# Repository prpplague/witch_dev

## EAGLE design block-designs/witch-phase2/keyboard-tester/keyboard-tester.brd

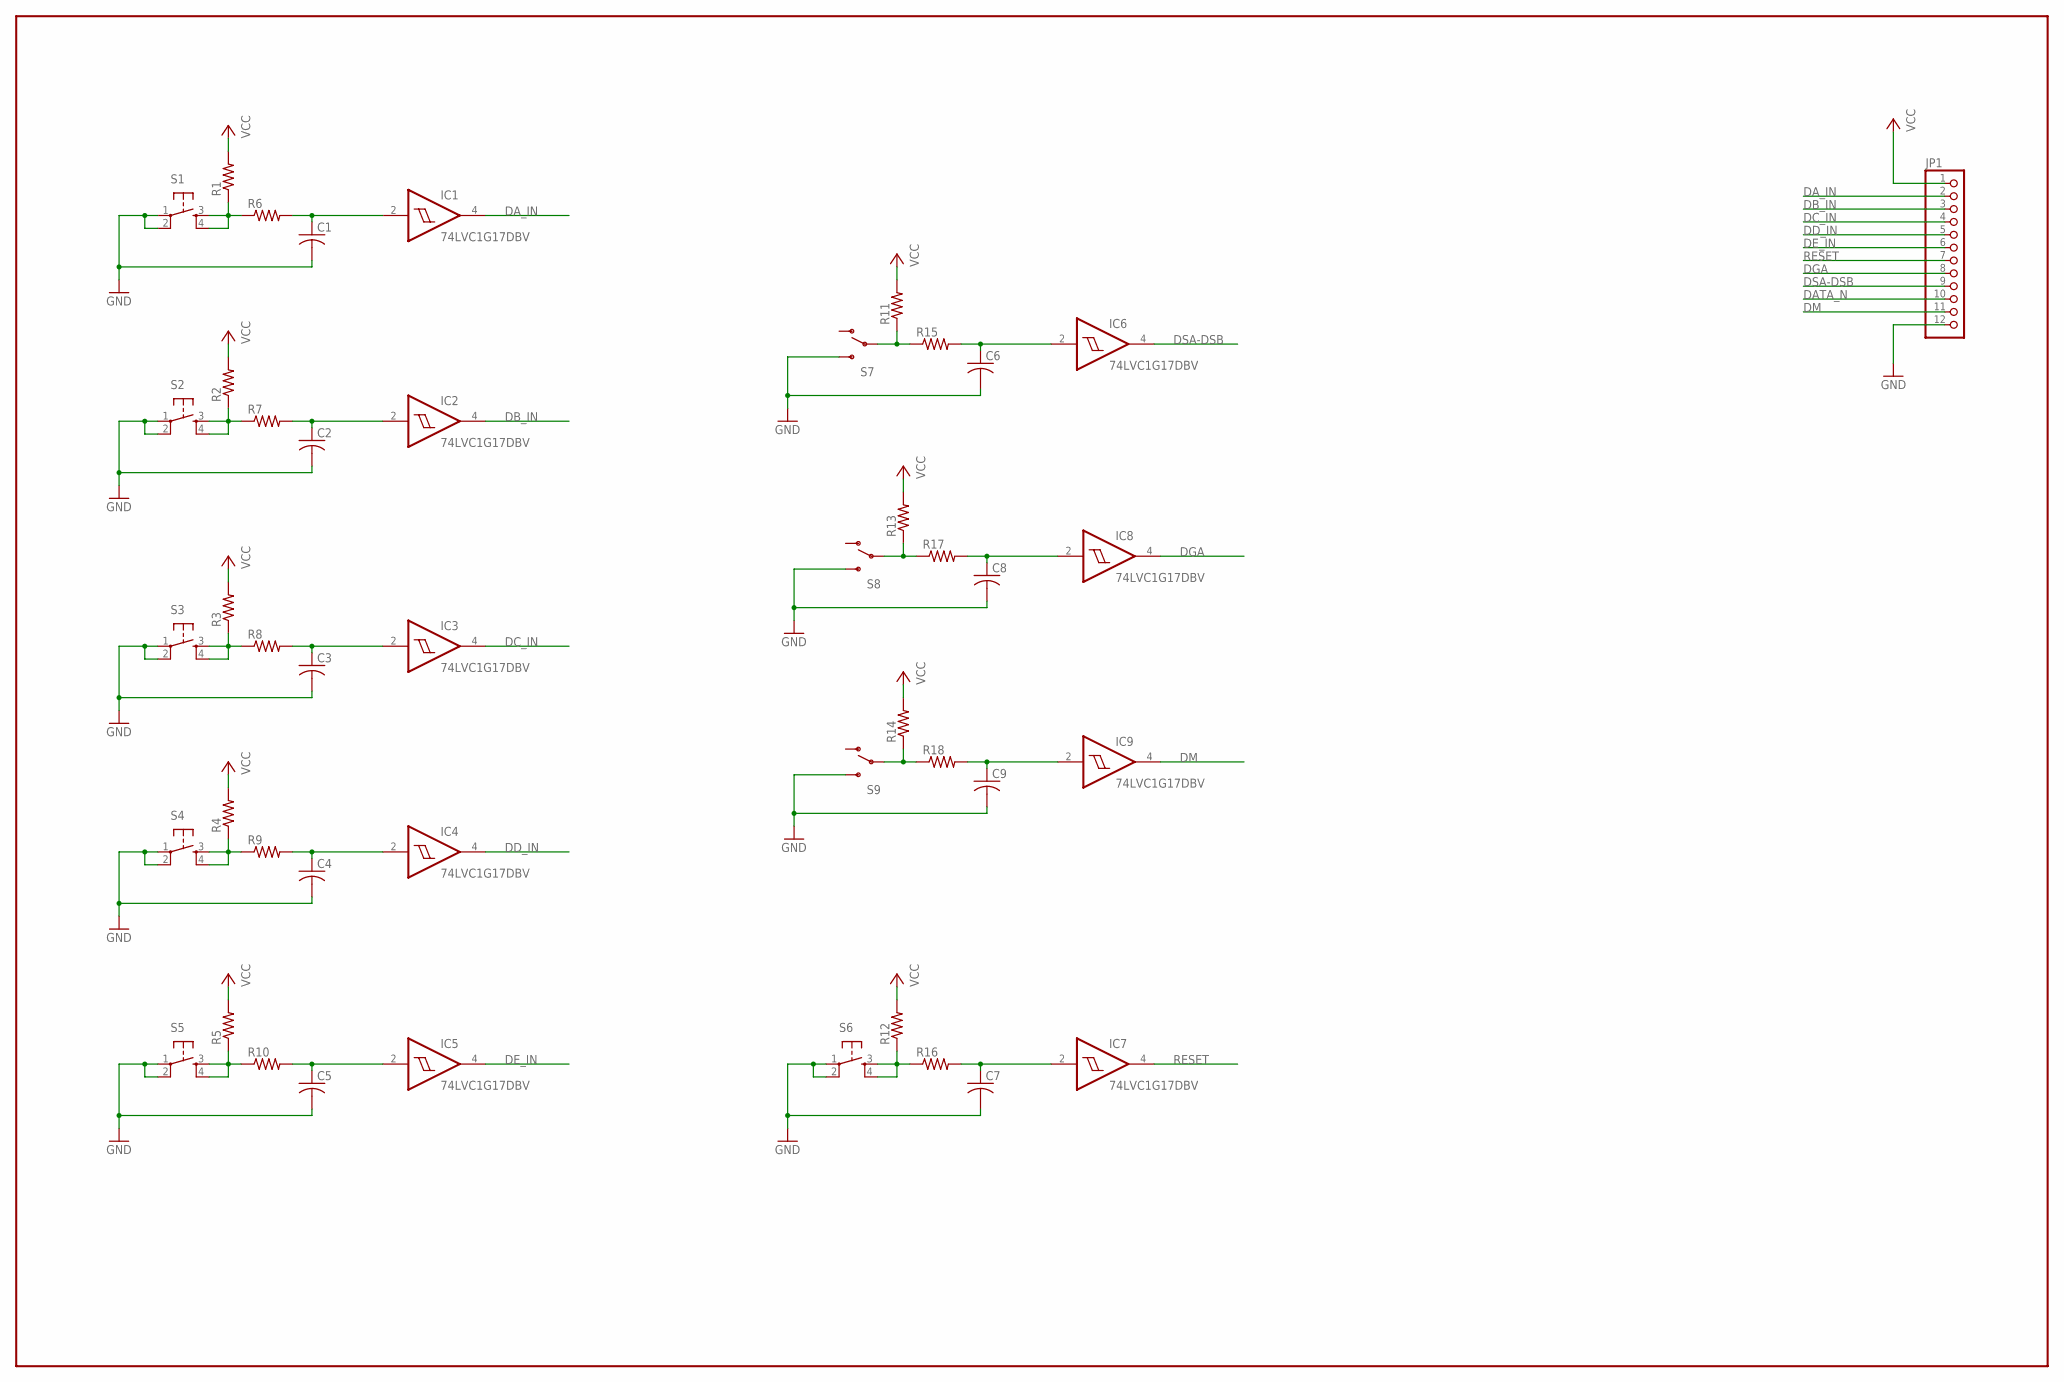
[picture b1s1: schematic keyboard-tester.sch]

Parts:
C1, C2, C3, C4, C5, C6, C7, C8, C9: C-USC0805; C0805
IC1, IC2, IC3, IC4, IC5, IC6, IC7, IC8, IC9: 74LVC1G17DBV; SOT23-5
JP1: PINHD-1X12; 1X12
R1, R2, R3, R4, R5, R6, R7, R8, R9, R10, R11, R12, R13, R14, R15, R16, R17, R18: R-US_R0805; R0805
S1, S2, S3, S4, S5, S6: TAC_SWITCHPTH; TACTILE-PTH
S7, S8, S9: SWITCH-SPDTPTH; SWITCH-SPDT

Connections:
DATA_N: JP1.10
DA_IN: IC1.4 (O), JP1.2
DB_IN: IC2.4 (O), JP1.3
DC_IN: IC3.4 (O), JP1.4
DD_IN: IC4.4 (O), JP1.5
DE_IN: IC5.4 (O), JP1.6
DGA: IC8.4 (O), JP1.8
DM: IC9.4 (O), JP1.11
DSA-DSB: IC6.4 (O), JP1.9
GND: C1.2, C2.2, C3.2, C4.2, C5.2, C6.2, C7.2, C8.2, C9.2, IC1.3 (GND), IC2.3 (GND), IC3.3 (GND), IC4.3 (GND), IC5.3 (GND), IC6.3 (GND), IC7.3 (GND), IC8.3 (GND), IC9.3 (GND), JP1.12, S1.1, S1.2, S2.1, S2.2, S3.1, S3.2, S4.1, S4.2, S5.1, S5.2, S6.1, S6.2, S7.3 (S), S8.3 (S), S9.3 (S)
unnamed: R1.1, R6.1, S1.3, S1.4
unnamed: C1.1, IC1.2 (I), R6.2
unnamed: C2.1, IC2.2 (I), R7.2
unnamed: R2.1, R7.1, S2.3, S2.4
unnamed: C3.1, IC3.2 (I), R8.2
unnamed: R3.1, R8.1, S3.3, S3.4
unnamed: C4.1, IC4.2 (I), R9.2
unnamed: R4.1, R9.1, S4.3, S4.4
unnamed: C5.1, IC5.2 (I), R10.2
unnamed: R5.1, R10.1, S5.3, S5.4
unnamed: C7.1, IC7.2 (I), R16.2
unnamed: R12.1, R16.1, S6.3, S6.4
unnamed: C6.1, IC6.2 (I), R15.2
unnamed: R11.1, R15.1, S7.2
unnamed: C8.1, IC8.2 (I), R17.2
unnamed: R13.1, R17.1, S8.2
unnamed: C9.1, IC9.2 (I), R18.2
unnamed: R14.1, R18.1, S9.2
RESET: IC7.4 (O), JP1.7
VCC: IC1.5 (VCC), IC2.5 (VCC), IC3.5 (VCC), IC4.5 (VCC), IC5.5 (VCC), IC6.5 (VCC), IC7.5 (VCC), IC8.5 (VCC), IC9.5 (VCC), JP1.1, R1.2, R2.2, R3.2, R4.2, R5.2, R11.2, R12.2, R13.2, R14.2

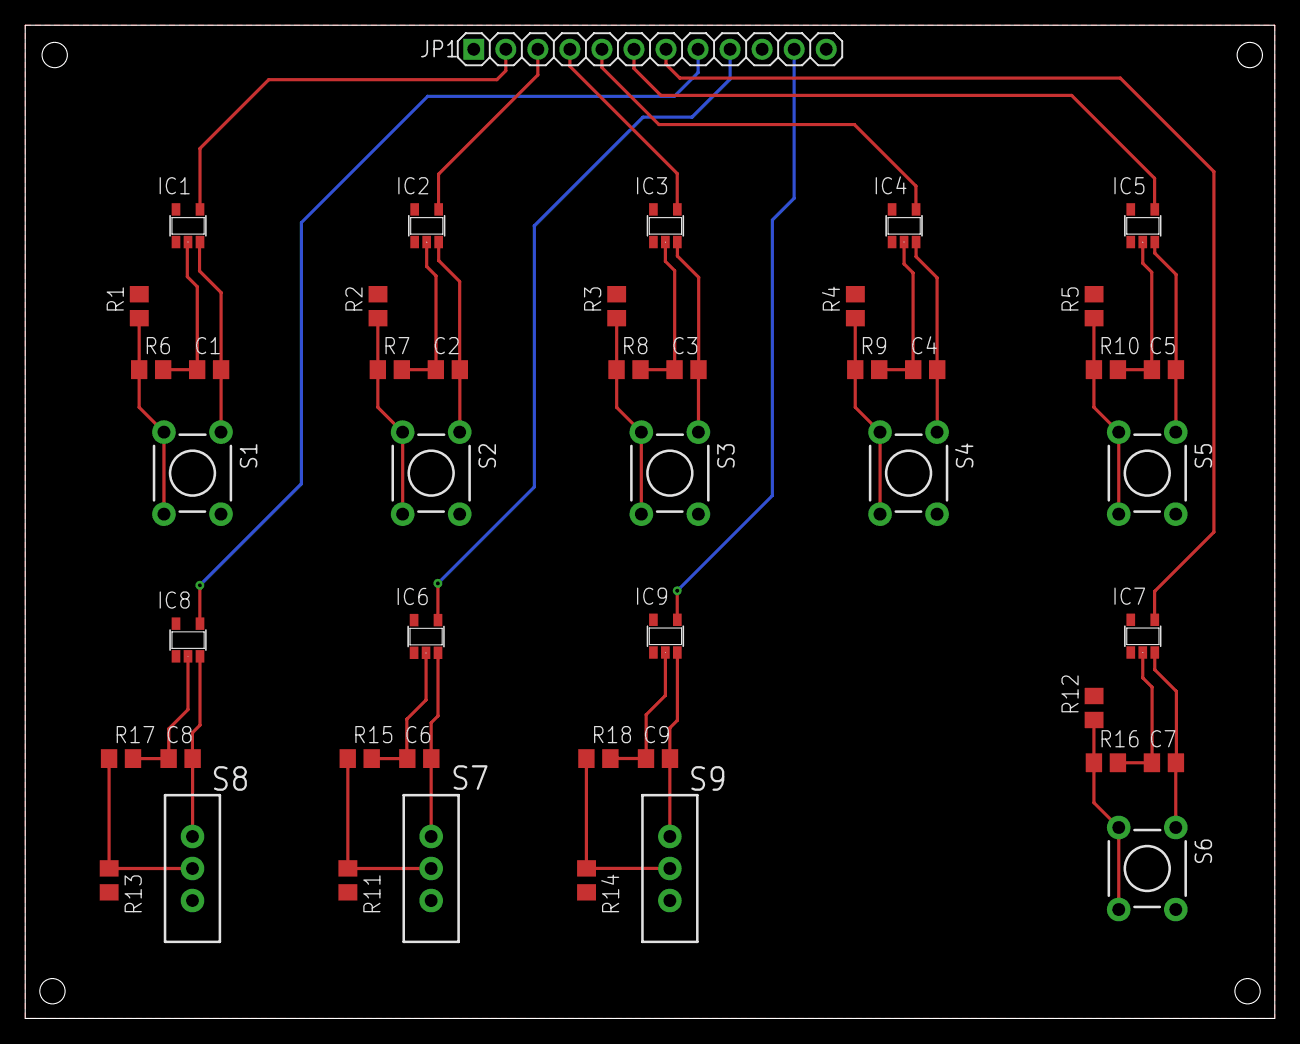
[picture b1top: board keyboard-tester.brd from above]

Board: 2 copper layers, 99.1 x 78.7 mm, 46 parts (0 on the bottom side), 29 nets.

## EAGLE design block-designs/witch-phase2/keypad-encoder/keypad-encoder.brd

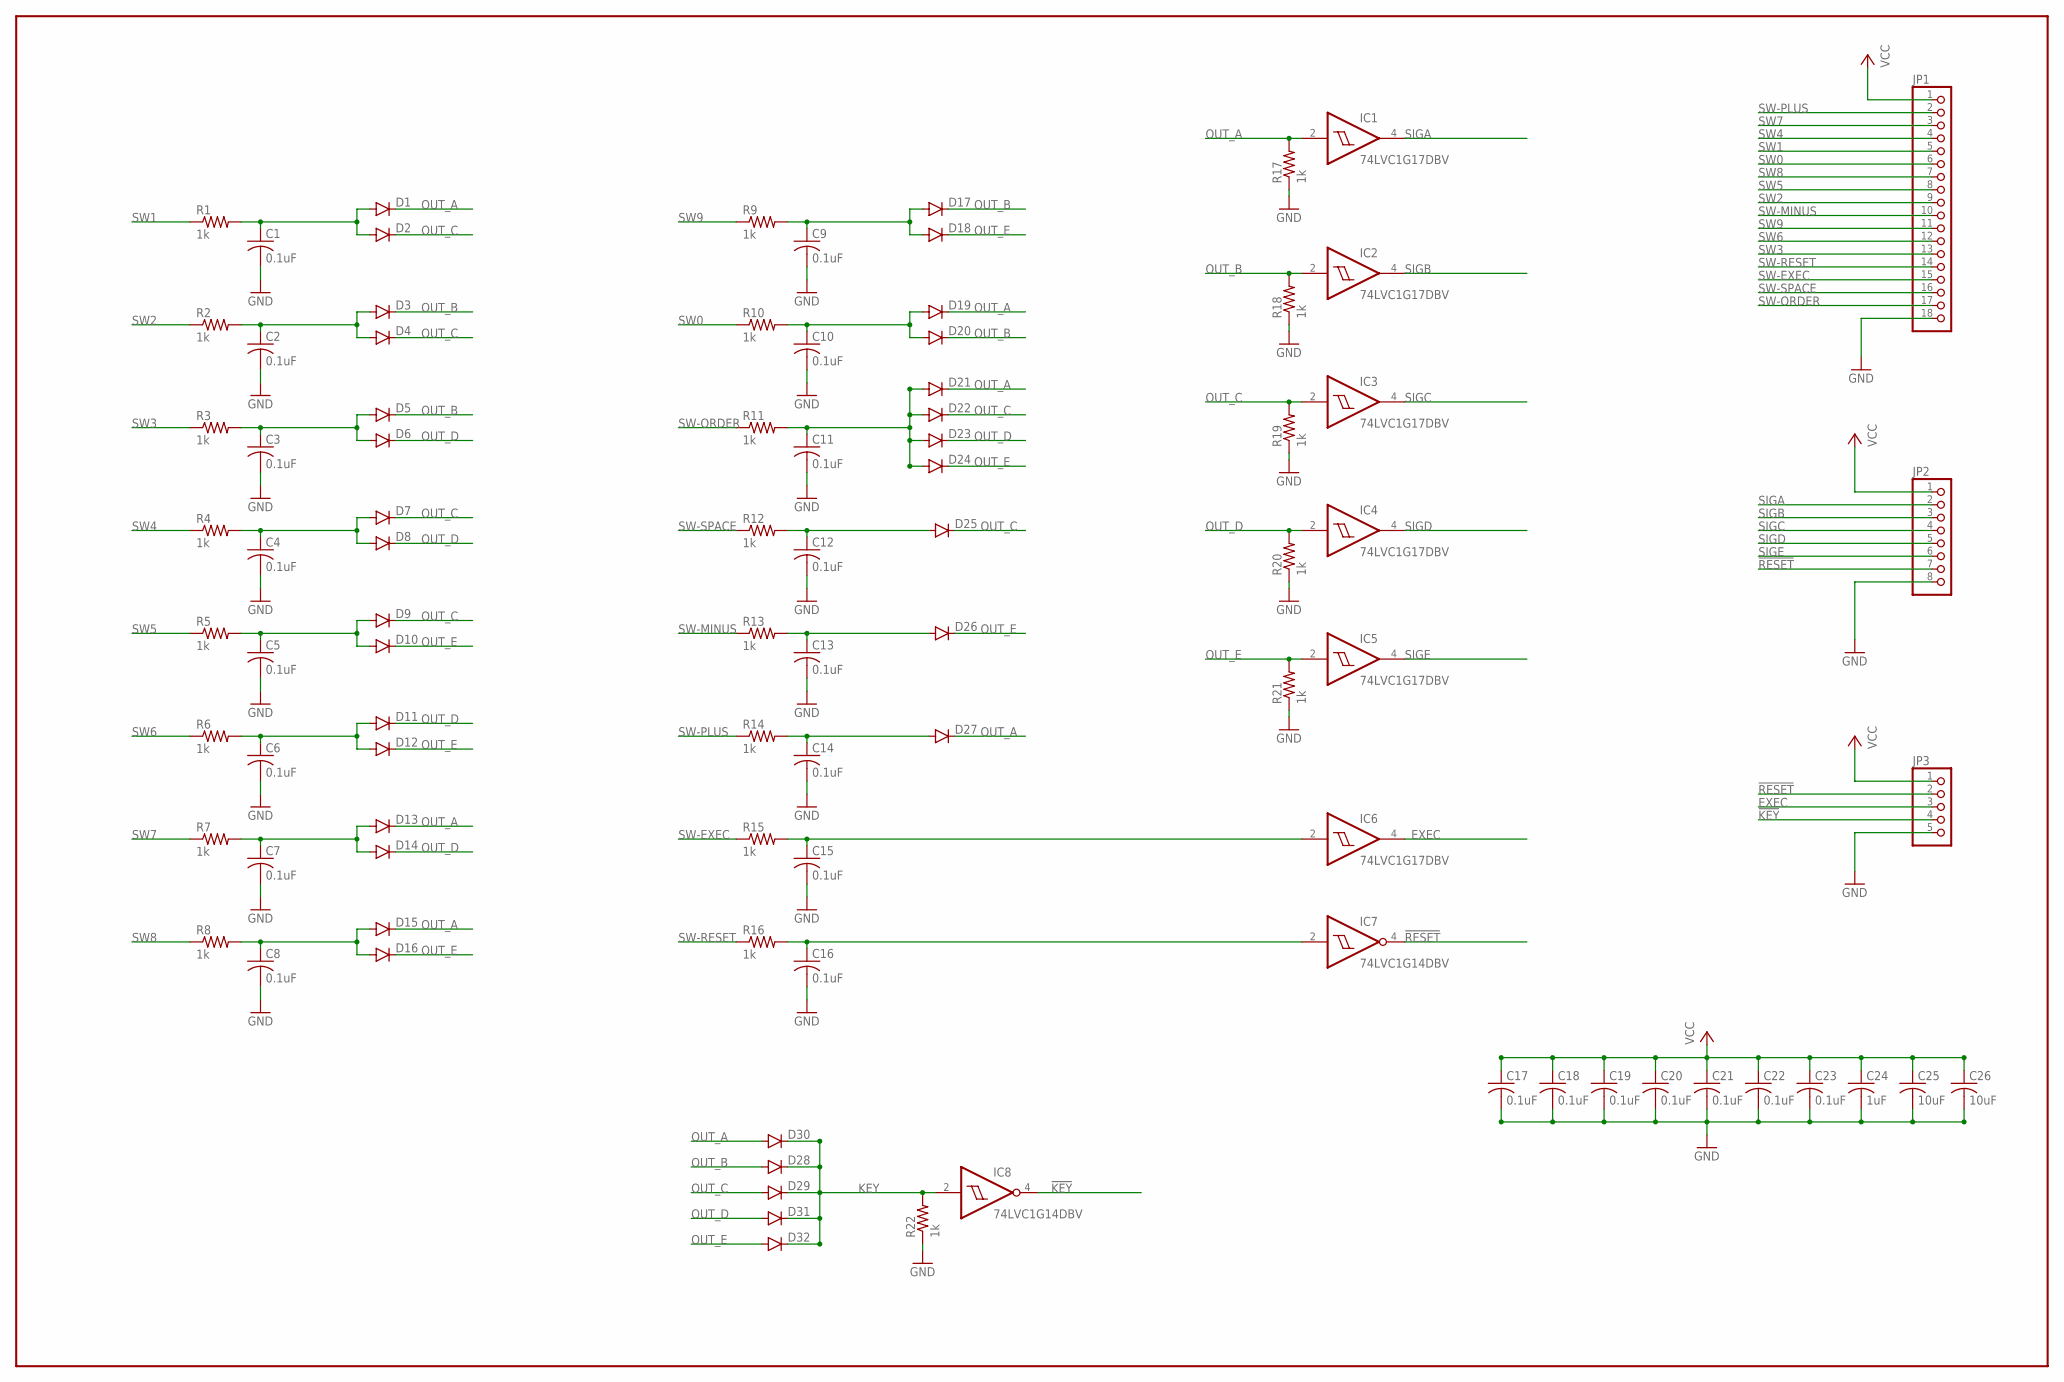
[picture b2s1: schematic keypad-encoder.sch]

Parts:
C1, C2, C3, C4, C5, C6, C7, C8, C9, C10, C11, C12, C13, C14, C15, C16, C17, C18, C19, C20, C21, C22, C23: 0.1uF; C0805
C24: 1uF; C0805
C25, C26: 10uF; C0805
D1, D2, D3, D4, D5, D6, D7, D8, D9, D10, D11, D12, D13, D14, D15, D16, D17, D18, D19, D20, D21, D22, D23, D24, D25, D26, D27, D28, D29, D30, D31, D32: DIODEPTH; DIODE-1N4001
IC1, IC2, IC3, IC4, IC5, IC6: 74LVC1G17DBV; SOT23-5
IC7, IC8: 74LVC1G14DBV; SOT23-5
JP1: PINHD-1X18; 1X18
JP2: PINHD-1X8; 1X08
JP3: PINHD-1X5; 1X05
R1, R2, R3, R4, R5, R6, R7, R8, R9, R10, R11, R12, R13, R14, R15, R16, R17, R18, R19, R20, R21, R22: 1k; R0805

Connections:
!KEY: IC8.4 (O), JP3.4
!RESET: IC7.4 (O), JP2.7, JP3.2
EXEC: IC6.4 (O), JP3.3
GND: C1.2, C2.2, C3.2, C4.2, C5.2, C6.2, C7.2, C8.2, C9.2, C10.2, C11.2, C12.2, C13.2, C14.2, C15.2, C16.2, C17.2, C18.2, C19.2, C20.2, C21.2, C22.2, C23.2, C24.2, C25.2, C26.2, IC1.3 (GND), IC2.3 (GND), IC3.3 (GND), IC4.3 (GND), IC5.3 (GND), IC6.3 (GND), IC7.3 (GND), IC8.3 (GND), JP1.18, JP2.8, JP3.5, R17.1, R18.1, R19.1, R20.1, R21.1, R22.1
KEY: D28.C, D29.C, D30.C, D31.C, D32.C, IC8.2 (I), R22.2
unnamed: C11.1, D21.A, D22.A, D23.A, D24.A, R11.2
unnamed: C1.1, D1.A, D2.A, R1.2
unnamed: C2.1, D3.A, D4.A, R2.2
unnamed: C3.1, D5.A, D6.A, R3.2
unnamed: C4.1, D7.A, D8.A, R4.2
unnamed: C5.1, D9.A, D10.A, R5.2
unnamed: C6.1, D11.A, D12.A, R6.2
unnamed: C7.1, D13.A, D14.A, R7.2
unnamed: C8.1, D15.A, D16.A, R8.2
unnamed: C9.1, D17.A, D18.A, R9.2
unnamed: C10.1, D19.A, D20.A, R10.2
unnamed: C12.1, D25.A, R12.2
unnamed: C13.1, D26.A, R13.2
unnamed: C14.1, D27.A, R14.2
unnamed: C15.1, IC6.2 (I), R15.2
unnamed: C16.1, IC7.2 (I), R16.2
OUT_A: D1.C, D13.C, D15.C, D19.C, D21.C, D27.C, D30.A, IC1.2 (I), R17.2
OUT_B: D3.C, D5.C, D17.C, D20.C, D28.A, IC2.2 (I), R18.2
OUT_C: D2.C, D4.C, D7.C, D9.C, D22.C, D25.C, D29.A, IC3.2 (I), R19.2
OUT_D: D6.C, D8.C, D11.C, D14.C, D23.C, D31.A, IC4.2 (I), R20.2
OUT_E: D10.C, D12.C, D16.C, D18.C, D24.C, D26.C, D32.A, IC5.2 (I), R21.2
SIGA: IC1.4 (O), JP2.2
SIGB: IC2.4 (O), JP2.3
SIGC: IC3.4 (O), JP2.4
SIGD: IC4.4 (O), JP2.5
SIGE: IC5.4 (O), JP2.6
SW0: JP1.6, R10.1
SW1: JP1.5, R1.1
SW2: JP1.9, R2.1
SW3: JP1.13, R3.1
SW4: JP1.4, R4.1
SW5: JP1.8, R5.1
SW6: JP1.12, R6.1
SW7: JP1.3, R7.1
SW8: JP1.7, R8.1
SW9: JP1.11, R9.1
SW-EXEC: JP1.15, R15.1
SW-MINUS: JP1.10, R13.1
SW-ORDER: JP1.17, R11.1
SW-PLUS: JP1.2, R14.1
SW-RESET: JP1.14, R16.1
SW-SPACE: JP1.16, R12.1
VCC: C17.1, C18.1, C19.1, C20.1, C21.1, C22.1, C23.1, C24.1, C25.1, C26.1, IC1.5 (VCC), IC2.5 (VCC), IC3.5 (VCC), IC4.5 (VCC), IC5.5 (VCC), IC6.5 (VCC), IC7.5 (VCC), IC8.5 (VCC), JP1.1, JP2.1, JP3.1

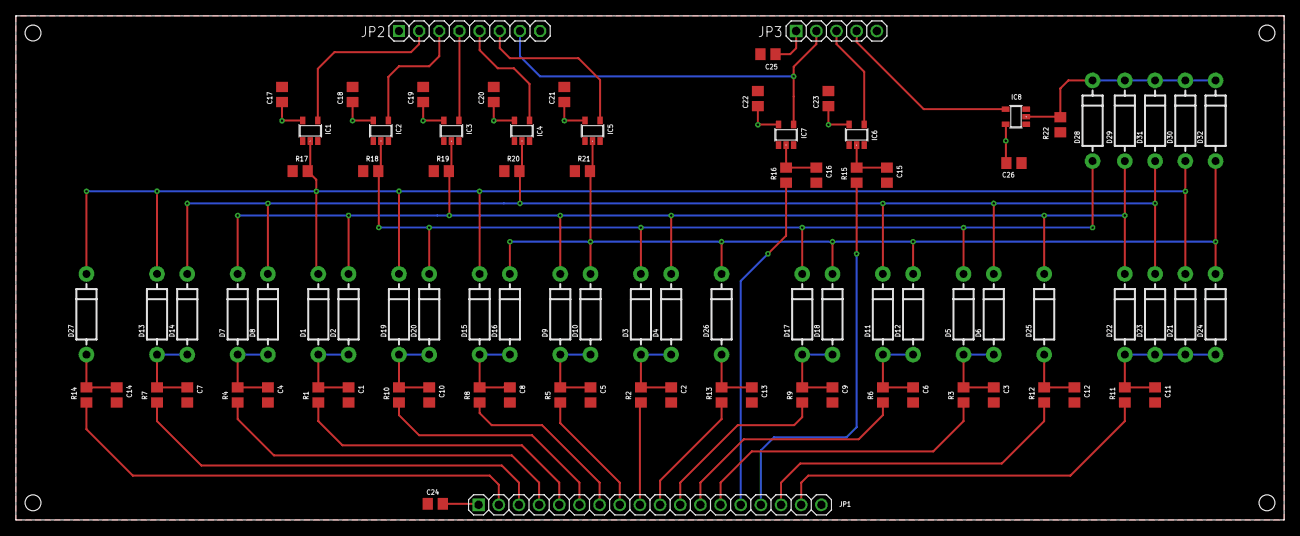
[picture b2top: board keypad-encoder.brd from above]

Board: 2 copper layers, 159.8 x 63.5 mm, 91 parts (0 on the bottom side), 48 nets.

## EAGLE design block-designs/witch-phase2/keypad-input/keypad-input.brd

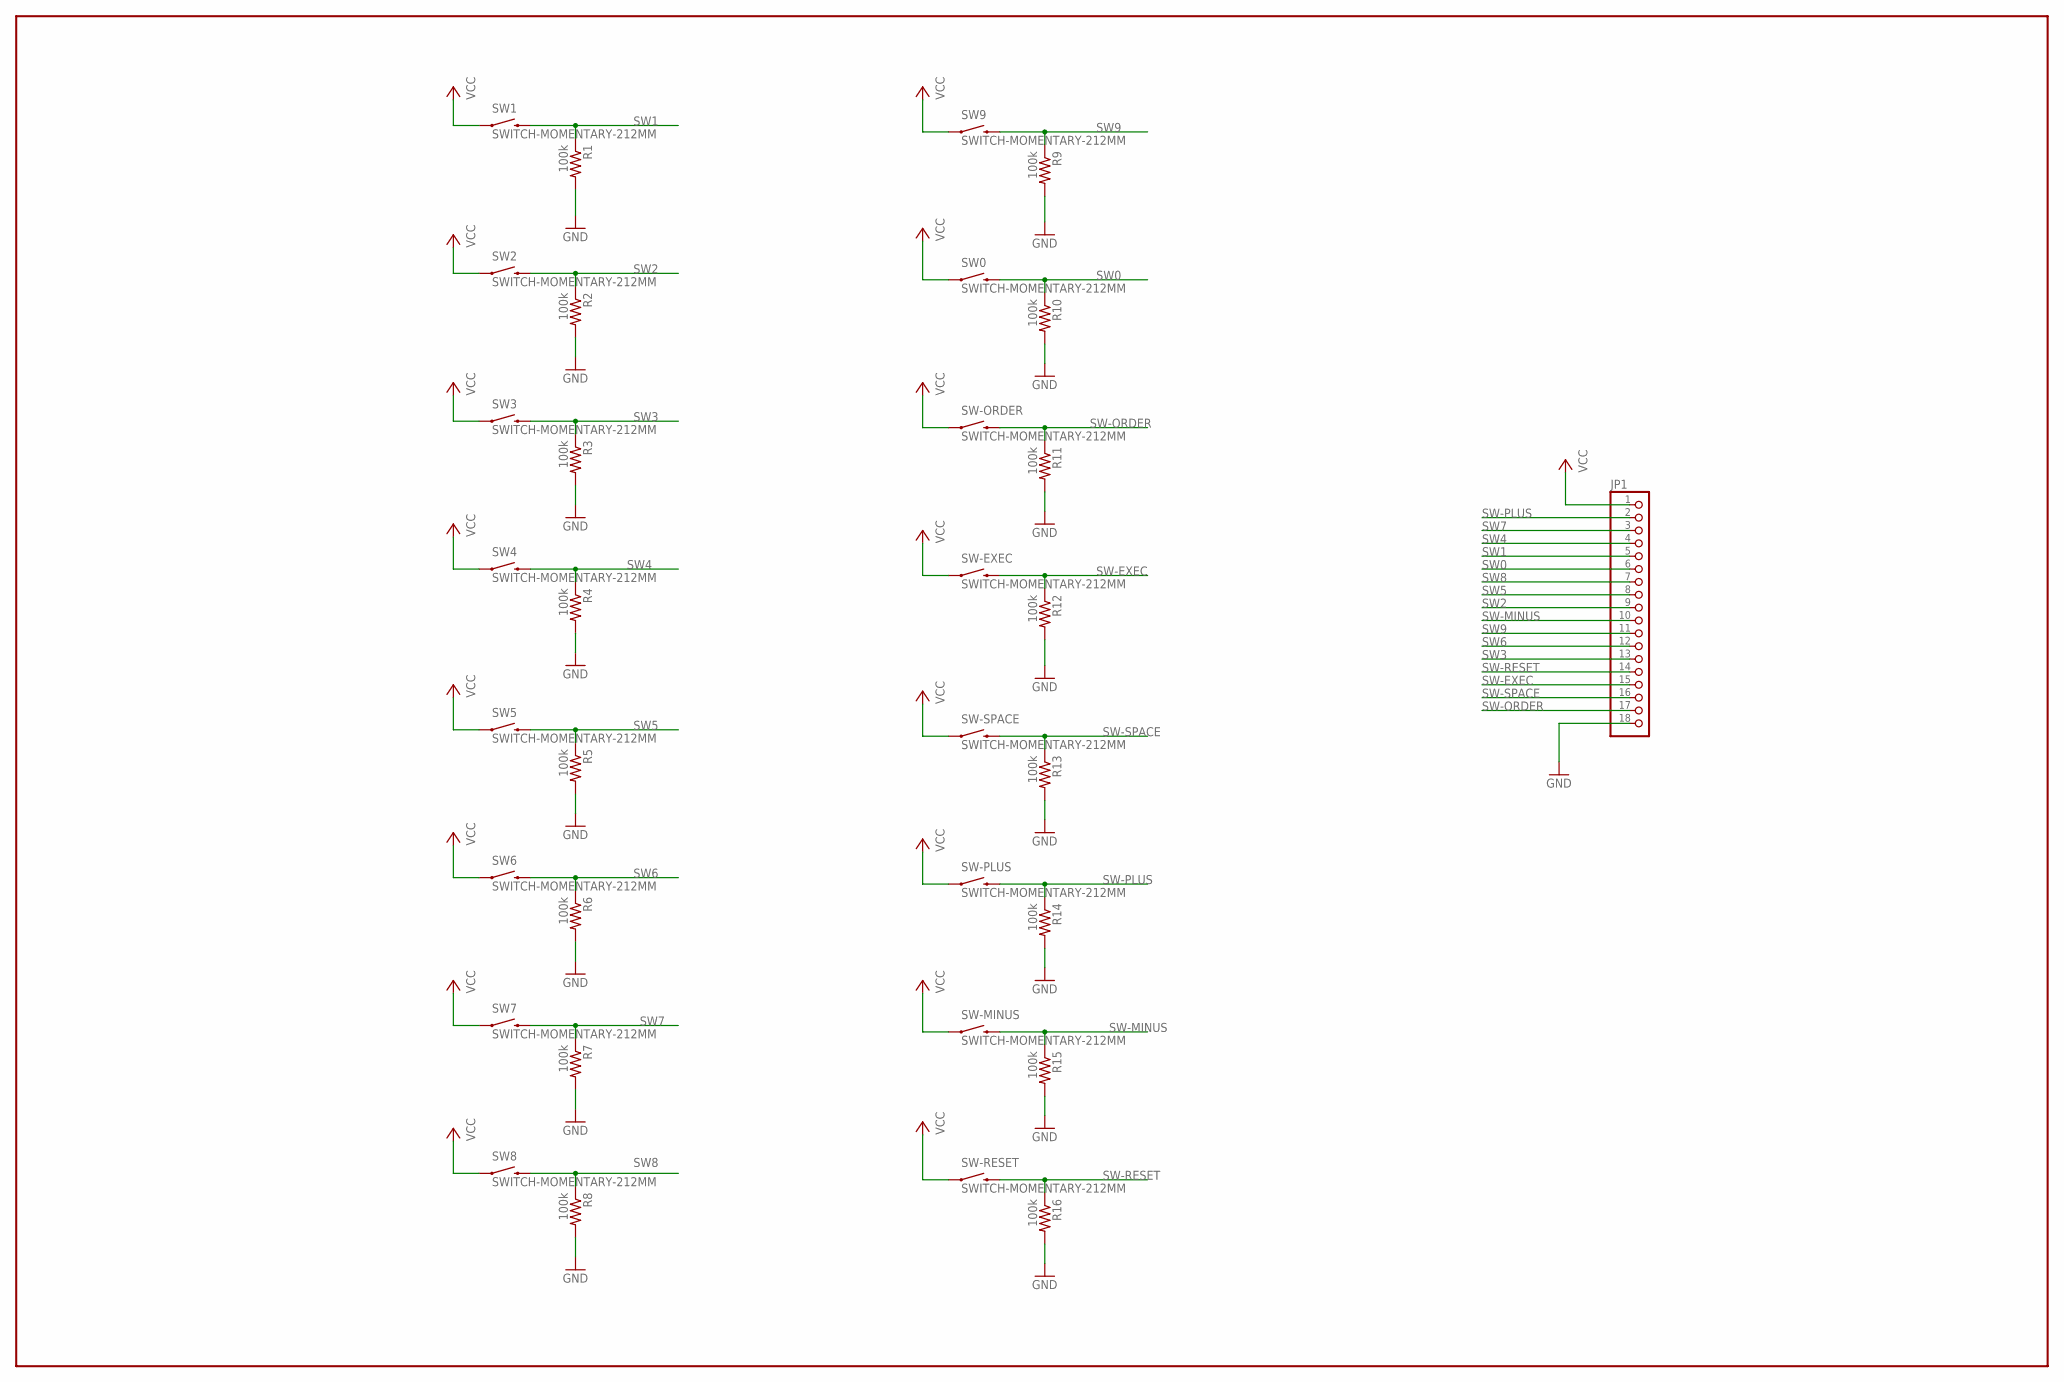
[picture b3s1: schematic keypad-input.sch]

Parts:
JP1: PINHD-1X18; 1X18
R1, R2, R3, R4, R5, R6, R7, R8, R9, R10, R11, R12, R13, R14, R15, R16: 100k; R0805
SW0, SW1, SW2, SW3, SW4, SW5, SW6, SW7, SW8, SW9: SWITCH-MOMENTARY-212MM; TACTILE-PTH-12MM
SW-EXEC: SWITCH-MOMENTARY-212MM; TACTILE-PTH-12MM
SW-MINUS: SWITCH-MOMENTARY-212MM; TACTILE-PTH-12MM
SW-ORDER: SWITCH-MOMENTARY-212MM; TACTILE-PTH-12MM
SW-PLUS: SWITCH-MOMENTARY-212MM; TACTILE-PTH-12MM
SW-RESET: SWITCH-MOMENTARY-212MM; TACTILE-PTH-12MM
SW-SPACE: SWITCH-MOMENTARY-212MM; TACTILE-PTH-12MM

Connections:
GND: JP1.18, R1.2, R2.2, R3.2, R4.2, R5.2, R6.2, R7.2, R8.2, R9.2, R10.2, R11.2, R12.2, R13.2, R14.2, R15.2, R16.2
SW0: JP1.6, R10.1, SW0.3 (2)
SW1: JP1.5, R1.1, SW1.3 (2)
SW2: JP1.9, R2.1, SW2.3 (2)
SW3: JP1.13, R3.1, SW3.3 (2)
SW4: JP1.4, R4.1, SW4.3 (2)
SW5: JP1.8, R5.1, SW5.3 (2)
SW6: JP1.12, R6.1, SW6.3 (2)
SW7: JP1.3, R7.1, SW7.3 (2)
SW8: JP1.7, R8.1, SW8.3 (2)
SW9: JP1.11, R9.1, SW9.3 (2)
SW-EXEC: JP1.15, R12.1, SW-EXEC.3 (2)
SW-MINUS: JP1.10, R15.1, SW-MINUS.3 (2)
SW-ORDER: JP1.17, R11.1, SW-ORDER.3 (2)
SW-PLUS: JP1.2, R14.1, SW-PLUS.3 (2)
SW-RESET: JP1.14, R16.1, SW-RESET.3 (2)
SW-SPACE: JP1.16, R13.1, SW-SPACE.3 (2)
VCC: JP1.1, SW0.1, SW1.1, SW2.1, SW3.1, SW4.1, SW5.1, SW6.1, SW7.1, SW8.1, SW9.1, SW-EXEC.1, SW-MINUS.1, SW-ORDER.1, SW-PLUS.1, SW-RESET.1, SW-SPACE.1

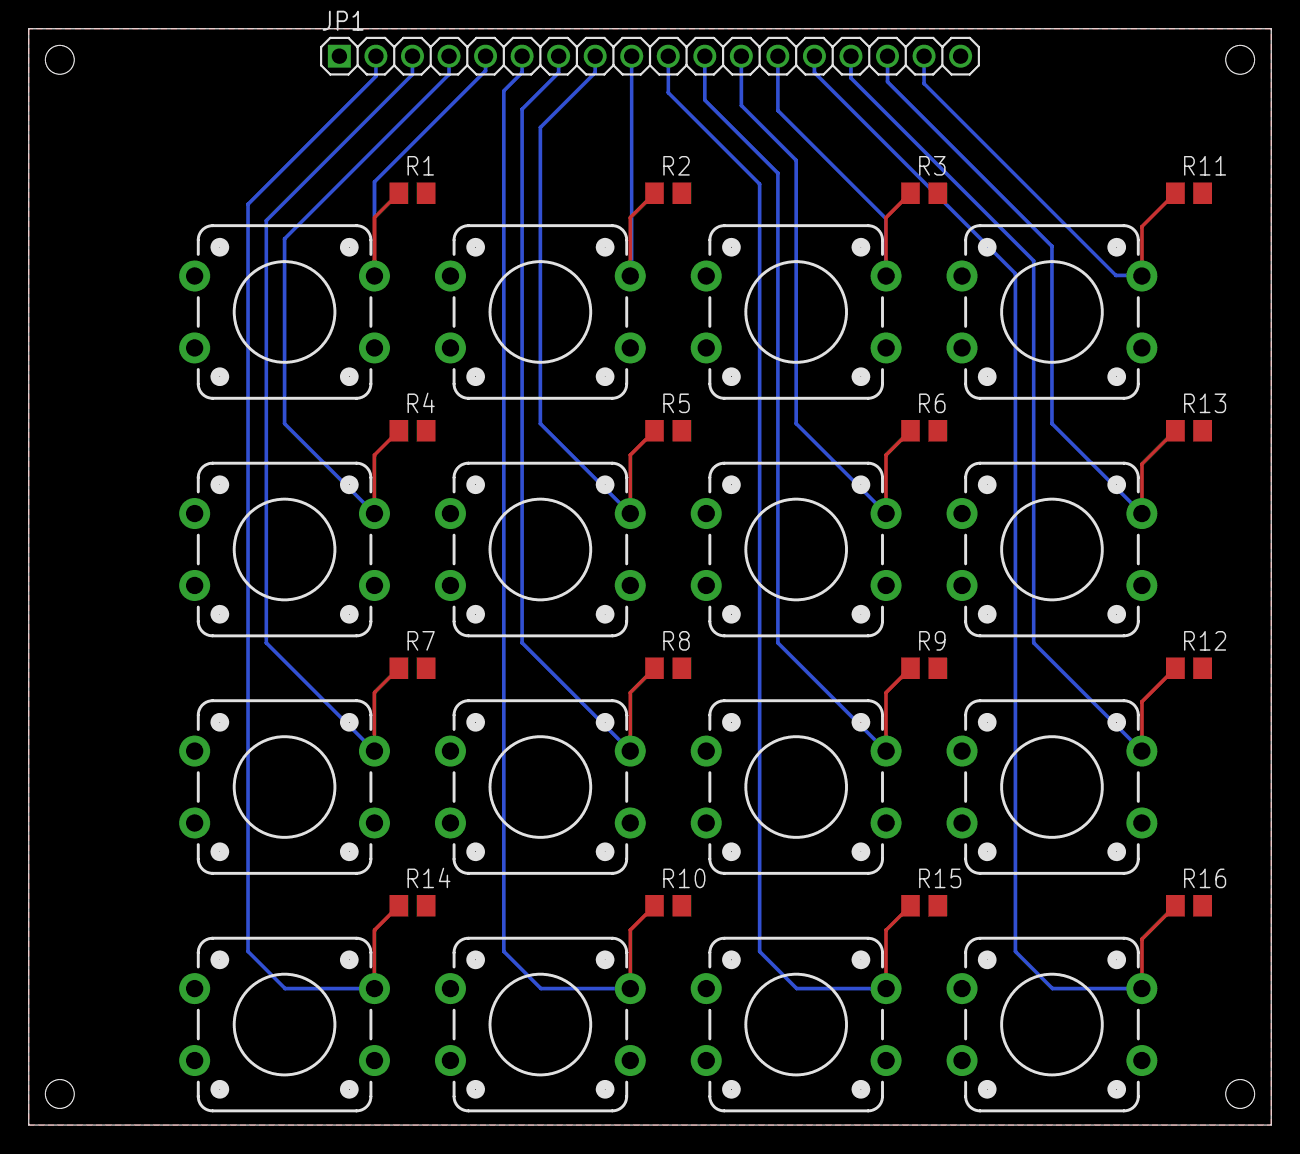
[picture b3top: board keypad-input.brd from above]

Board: 2 copper layers, 86.4 x 76.2 mm, 33 parts (0 on the bottom side), 18 nets.

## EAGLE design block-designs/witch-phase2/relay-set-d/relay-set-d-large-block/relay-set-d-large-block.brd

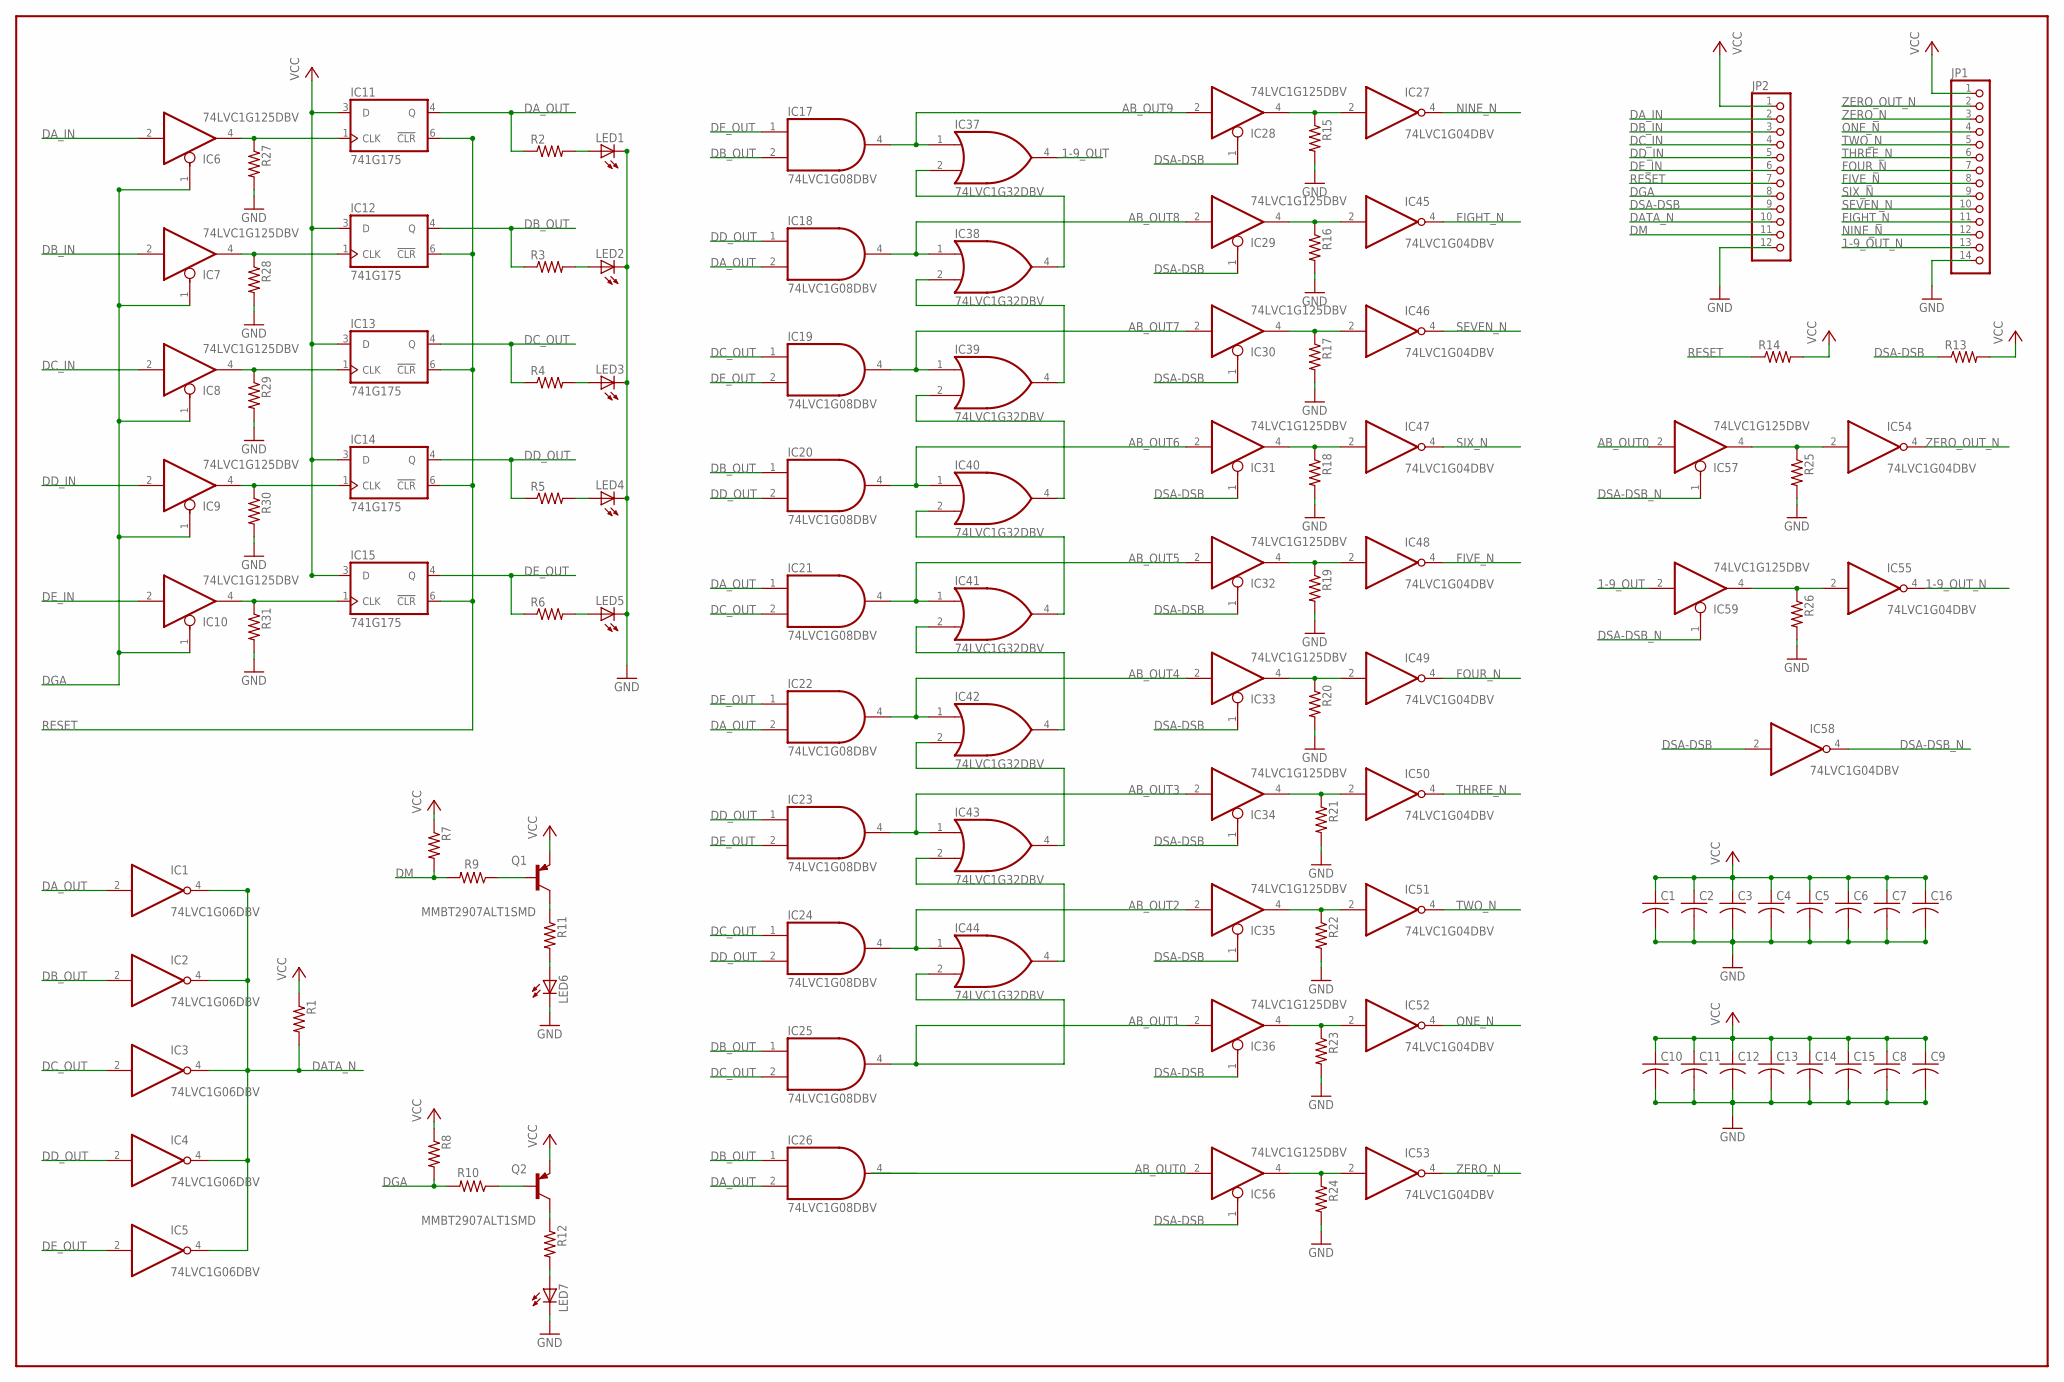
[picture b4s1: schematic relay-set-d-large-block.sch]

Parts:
C1, C2, C3, C4, C5, C6, C7, C8, C9, C10, C11, C12, C13, C14, C15, C16: C-USC0805; C0805
IC1, IC2, IC3, IC4, IC5: 74LVC1G06DBV; SOT23-5
IC6, IC7, IC8, IC9, IC10, IC28, IC29, IC30, IC31, IC32, IC33, IC34, IC35, IC36, IC56, IC57, IC59: 74LVC1G125DBV; SOT23-5
IC11, IC12, IC13, IC14, IC15: 741G175; DBV_R-PDSO-G6
IC17, IC18, IC19, IC20, IC21, IC22, IC23, IC24, IC25, IC26: 74LVC1G08DBV; SOT23-5
IC27, IC45, IC46, IC47, IC48, IC49, IC50, IC51, IC52, IC53, IC54, IC55, IC58: 74LVC1G04DBV; SOT23-5
IC37, IC38, IC39, IC40, IC41, IC42, IC43, IC44: 74LVC1G32DBV; SOT23-5
JP1: PINHD-1X14; 1X14
JP2: PINHD-1X12; 1X12
LED1, LED2, LED3, LED4, LED5, LED6, LED7: LEDCHIP-LED0805; CHIP-LED0805
Q1, Q2: MMBT2907ALT1SMD; SOT23-BEC
R1, R2, R3, R4, R5, R6, R7, R8, R9, R10, R11, R12, R13, R14, R15, R16, R17, R18, R19, R20, R21, R22, R23, R24, R25, R26, R27, R28, R29, R30, R31: R-US_R0805; R0805

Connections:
1-9_OUT: IC37.4 (O), IC59.2 (I)
1-9_OUT_N: IC55.4 (O), JP1.13
AB_OUT: IC26.4 (O)
AB_OUT0: IC56.2 (I), IC57.2 (I)
AB_OUT1: IC25.4 (O), IC36.2 (I), IC44.2 (I1)
AB_OUT2: IC24.4 (O), IC35.2 (I), IC44.1 (I0)
AB_OUT3: IC23.4 (O), IC34.2 (I), IC43.1 (I0)
AB_OUT4: IC22.4 (O), IC33.2 (I), IC42.1 (I0)
AB_OUT5: IC21.4 (O), IC32.2 (I), IC41.1 (I0)
AB_OUT6: IC20.4 (O), IC31.2 (I), IC40.1 (I0)
AB_OUT7: IC19.4 (O), IC30.2 (I), IC39.1 (I0)
AB_OUT8: IC18.4 (O), IC29.2 (I), IC38.1 (I0)
AB_OUT9: IC17.4 (O), IC28.2 (I), IC37.1 (I0)
DA: IC6.4 (O), IC11.1 (CLK), R27.1
DATA_N: IC1.4 (O), IC2.4 (O), IC3.4 (O), IC4.4 (O), IC5.4 (O), JP2.10, R1.2
DA_IN: IC6.2 (I), JP2.2
DA_OUT: IC1.2 (I), IC11.4 (Q), IC18.2 (I1), IC21.1 (I0), IC22.2 (I1), IC26.2 (I1), R2.1
DB: IC7.4 (O), IC12.1 (CLK), R28.1
DB_IN: IC7.2 (I), JP2.3
DB_OUT: IC2.2 (I), IC12.4 (Q), IC17.2 (I1), IC20.1 (I0), IC25.1 (I0), IC26.1 (I0), R3.1
DC: IC8.4 (O), IC13.1 (CLK), R29.1
DC_IN: IC8.2 (I), JP2.4
DC_OUT: IC3.2 (I), IC13.4 (Q), IC19.1 (I0), IC21.2 (I1), IC24.1 (I0), IC25.2 (I1), R4.1
DD: IC9.4 (O), IC14.1 (CLK), R30.1
DD_IN: IC9.2 (I), JP2.5
DD_OUT: IC4.2 (I), IC14.4 (Q), IC18.1 (I0), IC20.2 (I1), IC23.1 (I0), IC24.2 (I1), R5.1
DE: IC10.4 (O), IC15.1 (CLK), R31.1
DE_IN: IC10.2 (I), JP2.6
DE_OUT: IC5.2 (I), IC15.4 (Q), IC17.1 (I0), IC19.2 (I1), IC22.1 (I0), IC23.2 (I1), R6.1
DGA: IC6.1 (OE), IC7.1 (OE), IC8.1 (OE), IC9.1 (OE), IC10.1 (OE), JP2.8, R8.2, R10.2
DM: JP2.11, R7.2, R9.2
DSA-DSB: IC28.1 (OE), IC29.1 (OE), IC30.1 (OE), IC31.1 (OE), IC32.1 (OE), IC33.1 (OE), IC34.1 (OE), IC35.1 (OE), IC36.1 (OE), IC56.1 (OE), IC58.2 (I), JP2.9, R13.1
DSA-DSB_N: IC57.1 (OE), IC58.4 (O), IC59.1 (OE)
EIGHT: IC29.4 (O), IC45.2 (I), R16.1
EIGHT_N: IC45.4 (O), JP1.11
FIVE: IC32.4 (O), IC48.2 (I), R19.1
FIVE_N: IC48.4 (O), JP1.8
FOUR: IC33.4 (O), IC49.2 (I), R20.1
FOUR_N: IC49.4 (O), JP1.7
GND: C1.2, C2.2, C3.2, C4.2, C5.2, C6.2, C7.2, C8.2, C9.2, C10.2, C11.2, C12.2, C13.2, C14.2, C15.2, C16.2, IC1.3 (GND), IC2.3 (GND), IC3.3 (GND), IC4.3 (GND), IC5.3 (GND), IC6.3 (GND), IC7.3 (GND), IC8.3 (GND), IC9.3 (GND), IC10.3 (GND), IC11.2 (GND), IC12.2 (GND), IC13.2 (GND), IC14.2 (GND), IC15.2 (GND), IC17.3 (GND), IC18.3 (GND), IC19.3 (GND), IC20.3 (GND), IC21.3 (GND), IC22.3 (GND), IC23.3 (GND), IC24.3 (GND), IC25.3 (GND), IC26.3 (GND), IC27.3 (GND), IC28.3 (GND), IC29.3 (GND), IC30.3 (GND), IC31.3 (GND), IC32.3 (GND), IC33.3 (GND), IC34.3 (GND), IC35.3 (GND), IC36.3 (GND), IC37.3 (GND), IC38.3 (GND), IC39.3 (GND), IC40.3 (GND), IC41.3 (GND), IC42.3 (GND), IC43.3 (GND), IC44.3 (GND), IC45.3 (GND), IC46.3 (GND), IC47.3 (GND), IC48.3 (GND), IC49.3 (GND), IC50.3 (GND), IC51.3 (GND), IC52.3 (GND), IC53.3 (GND), IC54.3 (GND), IC55.3 (GND), IC56.3 (GND), IC57.3 (GND), IC58.3 (GND), IC59.3 (GND), JP1.14, JP2.12, LED1.C, LED2.C, LED3.C, LED4.C, LED5.C, LED6.C, LED7.C, R15.2, R16.2, R17.2, R18.2, R19.2, R20.2, R21.2, R22.2, R23.2, R24.2, R25.2, R26.2, R27.2, R28.2, R29.2, R30.2, R31.2
unnamed: IC40.2 (I1), IC41.4 (O)
unnamed: IC41.2 (I1), IC42.4 (O)
unnamed: IC42.2 (I1), IC43.4 (O)
unnamed: IC43.2 (I1), IC44.4 (O)
unnamed: Q2.B, R10.1
unnamed: IC37.2 (I1), IC38.4 (O)
unnamed: IC38.2 (I1), IC39.4 (O)
unnamed: IC39.2 (I1), IC40.4 (O)
unnamed: LED1.A, R2.2
unnamed: LED2.A, R3.2
unnamed: LED3.A, R4.2
unnamed: Q2.C, R12.1
unnamed: LED7.A, R12.2
unnamed: Q1.B, R9.1
unnamed: Q1.C, R11.1
unnamed: LED6.A, R11.2
unnamed: LED4.A, R5.2
unnamed: LED5.A, R6.2
NINE: IC27.2 (I), IC28.4 (O), R15.1
NINE_N: IC27.4 (O), JP1.12
ONE: IC36.4 (O), IC52.2 (I), R23.1
ONE_N: IC52.4 (O), JP1.4
OUT0: IC54.2 (I), IC57.4 (O), R25.1
OUT1-9: IC55.2 (I), IC59.4 (O), R26.1
RESET: IC11.6 (!CLR), IC12.6 (!CLR), IC13.6 (!CLR), IC14.6 (!CLR), IC15.6 (!CLR), JP2.7, R14.1
SEVEN: IC30.4 (O), IC46.2 (I), R17.1
SEVEN_N: IC46.4 (O), JP1.10
SIX: IC31.4 (O), IC47.2 (I), R18.1
SIX_N: IC47.4 (O), JP1.9
THREE: IC34.4 (O), IC50.2 (I), R21.1
THREE_N: IC50.4 (O), JP1.6
TWO: IC35.4 (O), IC51.2 (I), R22.1
TWO_N: IC51.4 (O), JP1.5
VCC: C1.1, C2.1, C3.1, C4.1, C5.1, C6.1, C7.1, C8.1, C9.1, C10.1, C11.1, C12.1, C13.1, C14.1, C15.1, C16.1, IC1.5 (VCC), IC2.5 (VCC), IC3.5 (VCC), IC4.5 (VCC), IC5.5 (VCC), IC6.5 (VCC), IC7.5 (VCC), IC8.5 (VCC), IC9.5 (VCC), IC10.5 (VCC), IC11.3 (D), IC11.5 (VCC), IC12.3 (D), IC12.5 (VCC), IC13.3 (D), IC13.5 (VCC), IC14.3 (D), IC14.5 (VCC), IC15.3 (D), IC15.5 (VCC), IC17.5 (VCC), IC18.5 (VCC), IC19.5 (VCC), IC20.5 (VCC), IC21.5 (VCC), IC22.5 (VCC), IC23.5 (VCC), IC24.5 (VCC), IC25.5 (VCC), IC26.5 (VCC), IC27.5 (VCC), IC28.5 (VCC), IC29.5 (VCC), IC30.5 (VCC), IC31.5 (VCC), IC32.5 (VCC), IC33.5 (VCC), IC34.5 (VCC), IC35.5 (VCC), IC36.5 (VCC), IC37.5 (VCC), IC38.5 (VCC), IC39.5 (VCC), IC40.5 (VCC), IC41.5 (VCC), IC42.5 (VCC), IC43.5 (VCC), IC44.5 (VCC), IC45.5 (VCC), IC46.5 (VCC), IC47.5 (VCC), IC48.5 (VCC), IC49.5 (VCC), IC50.5 (VCC), IC51.5 (VCC), IC52.5 (VCC), IC53.5 (VCC), IC54.5 (VCC), IC55.5 (VCC), IC56.5 (VCC), IC57.5 (VCC), IC58.5 (VCC), IC59.5 (VCC), JP1.1, JP2.1, Q1.E, Q2.E, R1.1, R7.1, R8.1, R13.2, R14.2
ZERO: IC53.2 (I), IC56.4 (O), R24.1
ZERO_N: IC53.4 (O), JP1.3
ZERO_OUT_N: IC54.4 (O), JP1.2

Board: 2 copper layers, 116 parts (8 on the bottom side), 76 nets, no tracks yet.

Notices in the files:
parts and their libraries:
SparkFun-Electromechanical: Licensing: CC v3.0 Share-Alike You are welcome to use this library for commercial purposes.
SparkFun-DiscreteSemi: Licensing: Creative Commons ShareAlike 4.0 International - https://creativecommons.org/licenses/by-sa/4.0
